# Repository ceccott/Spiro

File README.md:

# Spiro
PIC24FJ256GA412 based board with Bluetooth, UART capabiliities, battery charging and pinned out analog channel.

### Schematic

### Board/CAD

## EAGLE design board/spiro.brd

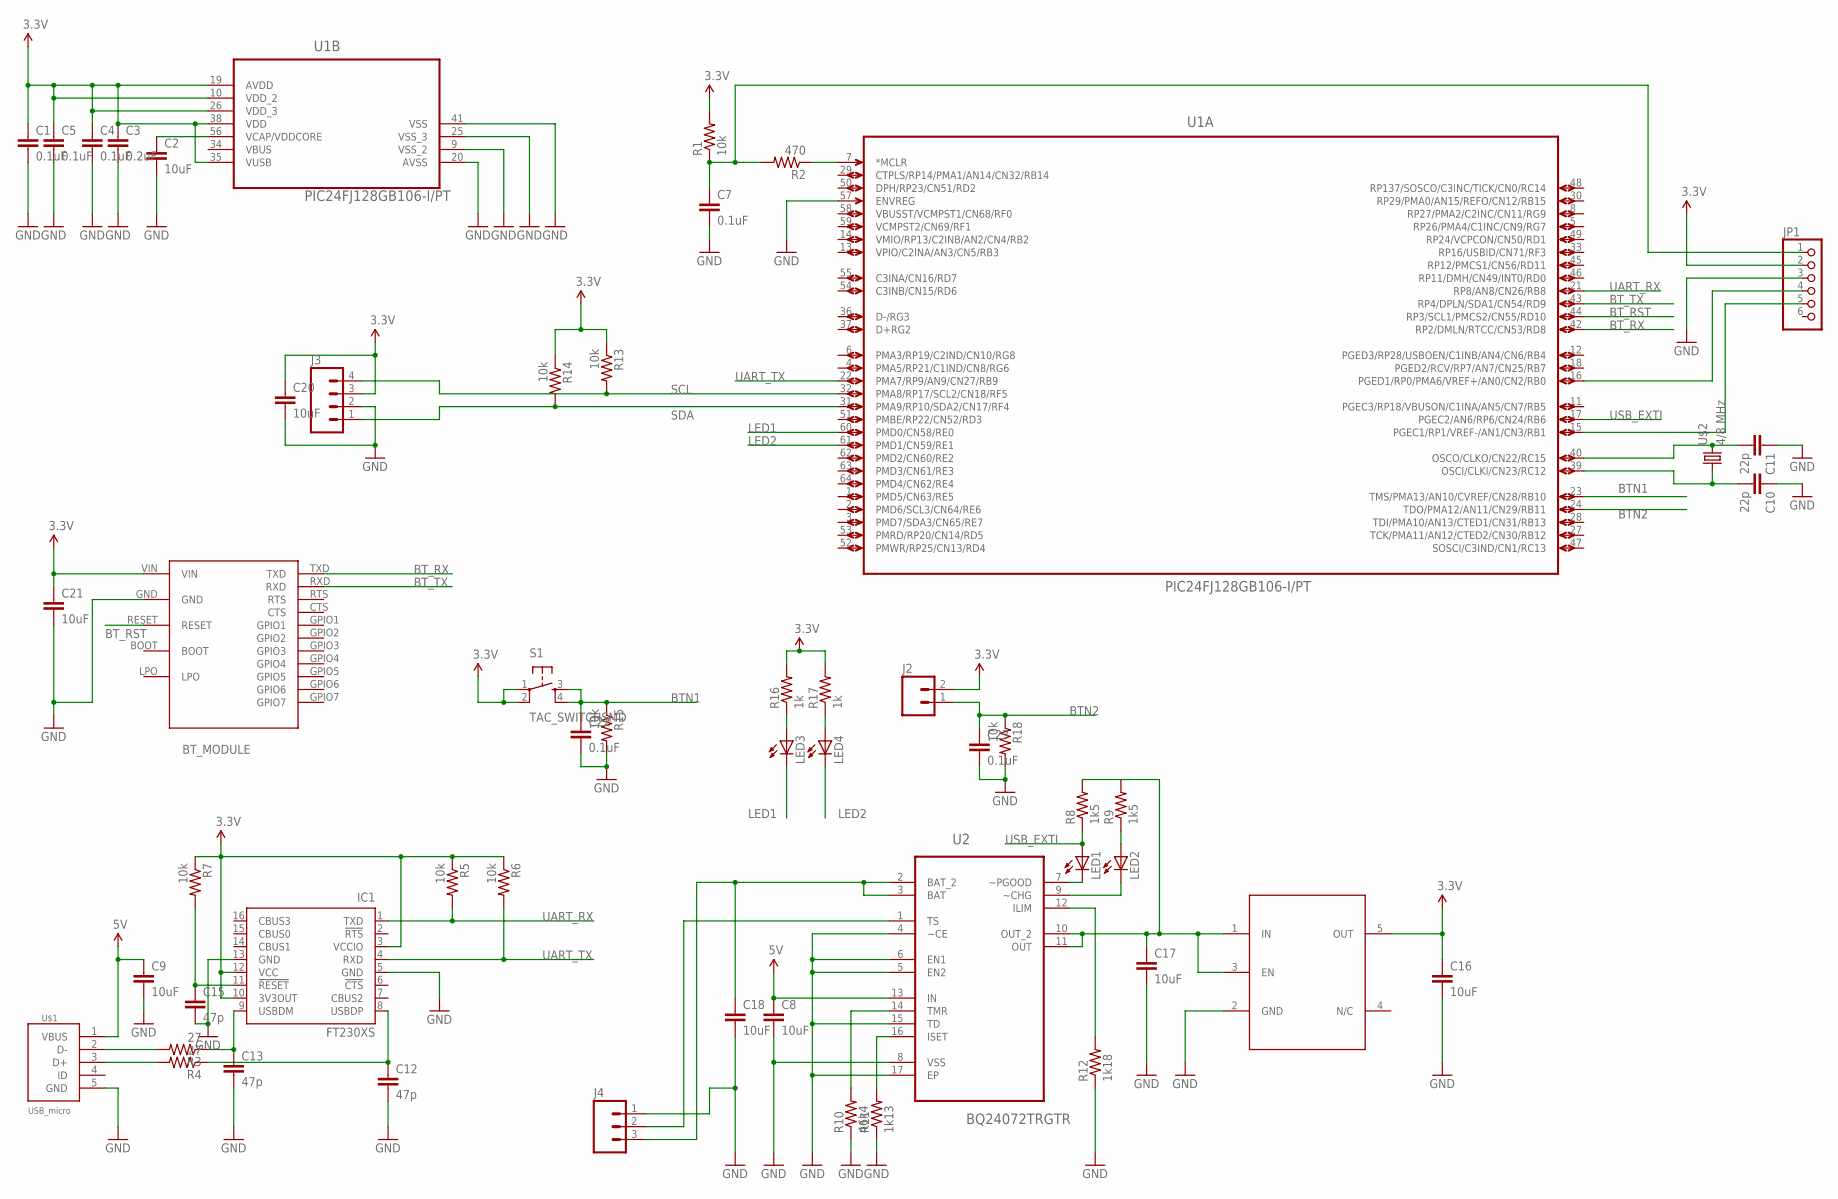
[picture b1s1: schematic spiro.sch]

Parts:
BT_MODULE: BT_MODULE; SPBT2632C2A
C1, C4, C5, C7, C22, C23: 0.1uF; 0603-CAP
C2, C8, C9, C16, C17, C18, C20, C21: 10uF; 1206
C3: 0.2uF; 0603-CAP
C10, C11: 22p; 0603-CAP
C12, C13, C15: 47p; 0603-CAP
IC1: FT230XS; SSOP16
J2: M02PTH; 1X02
J3: M04NO_SILK_ALL_ROUND; 1X04_NO_SILK_ALL_ROUND
J4: M03; 1X03-SMD-50MILS
JP1: PINHD-1X6; 1X06
LED1, LED2, LED3, LED4: LEDCHIP-LED0603; CHIP-LED0603
R1, R5, R6, R7, R13, R14, R15, R18: 10k; 0603-RES
R2: 470; 0603-RES
R3, R4: 27; 0603-RES
R8, R9: 1k5; 0603-RES
R10: 46k4; 0603-RES
R11: 1k13; 0603-RES
R12: 1k18; 0603-RES
R16, R17: 1k; 0603-RES
S1: TAC_SWITCHSMD; TACTILE-SWITCH-SMD
U1: PIC24FJ128GB106-I/PT; QFP50P1200X1200X120-64N
U2: BQ24072TRGTR; QFN50P300X300X100-17N
U$1: USB_micro; USB-MICRO-MOLEX-105017-0001
U$2: 4/8 MHz; CRYSTAL-SMD-6X3.5-2SMX
U$3: LP3990; SOT95P280X145-5N

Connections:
3.3V: BT_MODULE.VIN, C1.1, C3.1, C4.1, C5.1, C16.1, C20.1, C21.1, IC1.3 (VCCIO), IC1.10 (3V3OUT), IC1.12 (VCC), J2.2, J3.3, JP1.2, R1.2, R5.1, R6.1, R7.1, R13.1, R14.1, R16.2, R17.2, S1.1, S1.2, U1.10 (VDD_2), U1.19 (AVDD), U1.26 (VDD_3), U1.35 (VUSB), U1.38 (VDD), U$3.5 (OUT)
5V: C8.1, C9.1, U2.13 (IN), U$1.1 (VBUS)
BTN1: C22.1, R15.1, S1.3, S1.4, U1.23 (TMS/PMA13/AN10/CVREF/CN28/RB10)
BTN2: C23.1, J2.1, R18.1, U1.24 (TDO/PMA12/AN11/CN29/RB11)
BT_RST: BT_MODULE.RESET, U1.44 (RP3/SCL1/PMCS2/CN55/RD10)
BT_RX: BT_MODULE.TXD, U1.42 (RP2/DMLN/RTCC/CN53/RD8)
BT_TX: BT_MODULE.RXD, U1.43 (RP4/DPLN/SDA1/CN54/RD9)
GND: BT_MODULE.GND, C1.2, C2.2, C3.2, C4.2, C5.2, C7.2, C8.2, C9.2, C10.1, C11.1, C12.2, C13.2, C15.2, C16.2, C17.2, C18.2, C20.2, C21.2, C22.2, C23.2, IC1.5 (GND), IC1.13 (GND), J3.2, J4.1 (3), JP1.3, R10.1, R11.1, R12.1, R15.2, R18.2, U1.9 (VSS_2), U1.20 (AVSS), U1.25 (VSS_3), U1.41 (VSS), U1.57 (ENVREG), U2.4 (~CE), U2.5 (EN2), U2.6 (EN1), U2.8 (VSS), U2.15 (TD), U2.17 (EP), U$1.5 (GND), U$3.2 (GND)
LED1: LED3.C, U1.60 (PMD0/CN58/RE0)
LED2: LED4.C, U1.61 (PMD1/CN59/RE1)
unnamed: C2.1, U1.56 (VCAP/VDDCORE)
unnamed: R4.2, U$1.3 (D+)
unnamed: C13.1, IC1.9 (USBDM), R3.1
unnamed: C12.1, IC1.8 (USBDP), R4.1
unnamed: R3.2, U$1.2 (D-)
unnamed: LED1.C, U2.7 (~PGOOD)
unnamed: C7.1, JP1.1, R1.1, R2.2
unnamed: R2.1, U1.7 (*MCLR)
unnamed: C11.2, U1.40 (OSCO/CLKO/CN22/RC15), U$2.P$3 (2)
unnamed: JP1.4, U1.16 (PGED1/RP0/PMA6/VREF+/AN0/CN2/RB0)
unnamed: C10.2, U1.39 (OSCI/CLKI/CN23/RC12), U$2.P$1 (1)
unnamed: JP1.5, U1.15 (PGEC1/RP1/VREF-/AN1/CN3/RB1)
unnamed: C17.1, R8.2, R9.2, U2.10 (OUT_2), U2.11 (OUT), U$3.1 (IN), U$3.3 (EN)
unnamed: C15.1, IC1.11 (!RESET), R7.2
unnamed: LED2.A, R9.1
unnamed: J4.2, U2.1 (TS)
unnamed: C18.1, J4.3 (1), U2.2 (BAT_2), U2.3 (BAT)
unnamed: LED2.C, U2.9 (~CHG)
unnamed: R11.2, U2.16 (ISET)
unnamed: R12.2, U2.12 (ILIM)
unnamed: R10.2, U2.14 (TMR)
unnamed: LED3.A, R16.1
unnamed: LED4.A, R17.1
SCL: J3.4, R13.2, U1.32 (PMA8/RP17/SCL2/CN18/RF5)
SDA: J3.1, R14.2, U1.31 (PMA9/RP10/SDA2/CN17/RF4)
UART_RX: IC1.1 (TXD), R5.2, U1.21 (RP8/AN8/CN26/RB8)
UART_TX: IC1.4 (RXD), R6.2, U1.22 (PMA7/RP9/AN9/CN27/RB9)
USB_EXTI: LED1.A, R8.1, U1.17 (PGEC2/AN6/RP6/CN24/RB6)
VBUS: U1.34 (VBUS)

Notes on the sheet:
BT_MODULE

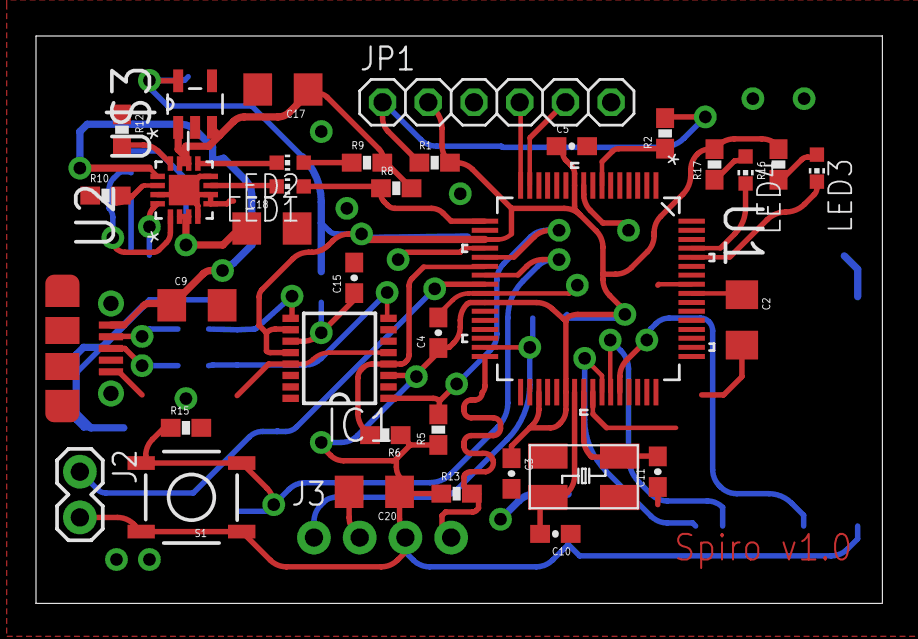
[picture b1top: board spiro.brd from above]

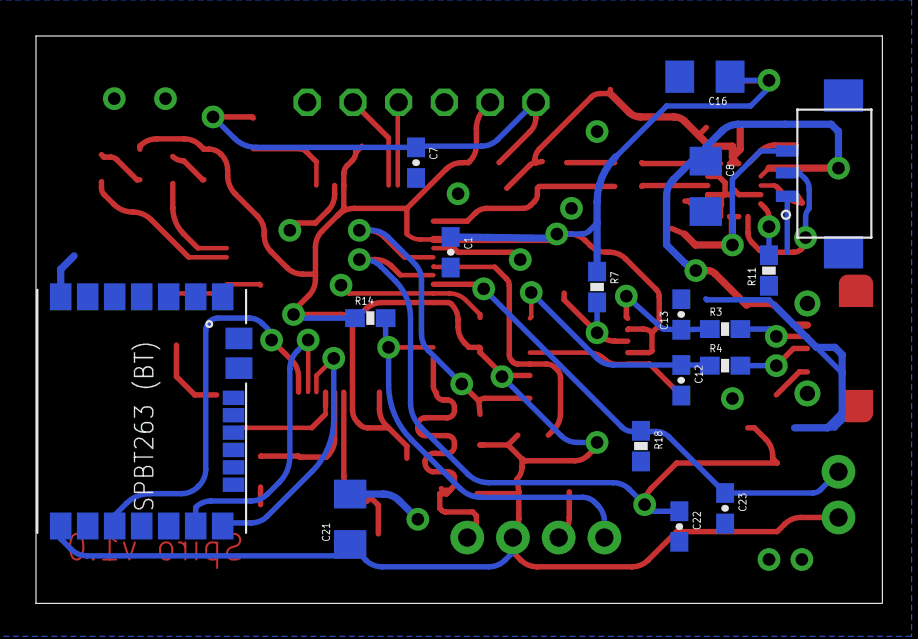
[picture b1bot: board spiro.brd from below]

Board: 2 copper layers, 47.0 x 31.5 mm, 54 parts (17 on the bottom side), 38 nets.

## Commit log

2019-09-06 init repo

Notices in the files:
parts and their libraries:
SparkFun-Capacitors: Licensing: Creative Commons ShareAlike 4.0 International - https://creativecommons.org/licenses/by-sa/4.0
